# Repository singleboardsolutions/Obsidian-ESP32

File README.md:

# Obsidian-ESP32
Design Files for Obsidian ESP32

Copyright Single Board Solutions LLC 2019
Licensed under CERN OHL v.1.2

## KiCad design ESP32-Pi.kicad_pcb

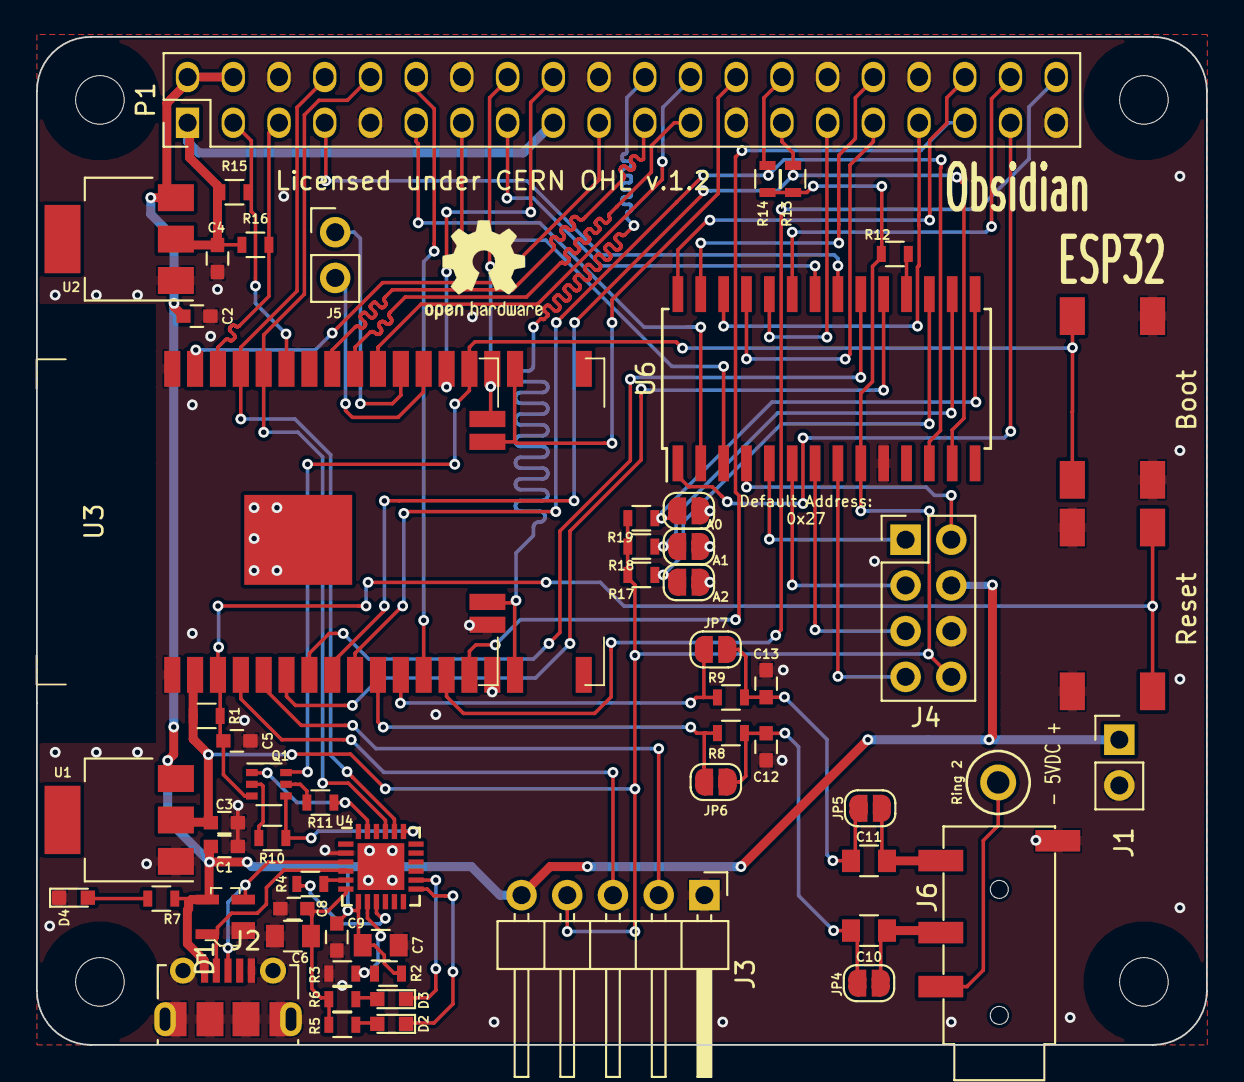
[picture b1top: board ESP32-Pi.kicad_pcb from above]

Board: 2 copper layers, 65.0 x 56.0 mm, 63 parts (0 on the bottom side), 71 nets.

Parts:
C1, C2: .22uF; C_0603
C3, C4, C5: .1uF; C_0603
C6, C7: 4.7uF; C_0805
C8, C9: 100nF; C_0603
C10, C11: 10 uF; C_0805
C12, C13: 10n; C_0603
D1: SP0503BAHTG; SOT-143-4
D2: LED_Green; LED_0603
D3: LED_Red; LED_0603
D4: LED_yellow; LED_0603
J1: PHX MPT 2.54mm 2pol; Pin_Header_Straight_1x02_Pitch2.54mm
J2: USB_B_Micro; USB_Micro-B_Molex-105017-0001
J3: 2.54mm 1x05 right angle; Pin_Header_Angled_1x05_Pitch2.54mm
J4: 2.54mm 2x04 straight; Pin_Header_Straight_2x04_Pitch2.54mm
J5: IO16/17; Pin_Header_Straight_1x02_Pitch2.54mm
J6: PJ320D; PJ320D_3.5mm_Jack
JP1: A2; SolderJumper-2_P1.3mm_Open_RoundedPad1.0x1.5mm
JP2: A1; SolderJumper-2_P1.3mm_Open_RoundedPad1.0x1.5mm
JP3: A0; SolderJumper-2_P1.3mm_Open_RoundedPad1.0x1.5mm
JP4, JP5, JP6, JP7: Bypass; SolderJumper-2_P1.3mm_Open_RoundedPad1.0x1.5mm
MK1, MK2, MK3, MK4: M2.5; MountingHole_2.7mm_M2.5
P1: 2.54mm 2x20 straight; PinHeader_2x20_P2.54mm_Vertical
Q1: MBT3904DW1; SOT-363_SC-70-6
R1, R4, R10, R11, R12, R17, R18, R19: 10k; R_0603
R2: 22.1k; R_0603
R3: 47.5k; R_0603
R5, R6, R7: 1k; R_0603
R8, R9: 220; R_0603
R13, R14, R15, R16: 1.8k; R_0603
Ring 2: Test_Point_Keystone_5010-5014_Multipurpose
SW1, SW2: 2-1437565-7; SW_FSM_JSM
U1, U2: AP2114H-3.3; SOT-223
U3: ESP32-WROOM-32; ESP32-WROOMVER-32D
U4: CP2102N-A01-GQFN24; QFN-24-1EP_4x4mm_Pitch0.5mm
U6: MCP23017_SO; SOIC-28W_7.5x17.9mm_Pitch1.27mm

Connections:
+3.3VP: C4.1, P1.1, P1.17, R15.1, R16.1, U2.2
+3V3: C3.1, J3.4, J4.8, R1.1, R12.1, R13.1, R14.1, R17.2, R18.2, R19.2, U1.2, U3.2, U6.9
+5V: C1.1, C2.1, C7.1, C9.1, D1.3, J1.1, J2.1, J3.5, J4.4, P1.2, P1.4, R2.1, R7.2, U1.3, U2.3, U4.7
/BCLK: P1.12, U3.12
/BOOT: Q1.6, SW1.1, U3.25
/DTR_PROG: Q1.1, R11.2, U4.23
/Exp_A0: JP3.1, R19.1, U6.15
/Exp_A1: JP2.1, R18.1, U6.16
/Exp_A2: JP1.1, R17.1, U6.17
/GPIO4(GCLK): P1.7, U6.21
/GPIO5: P1.29, U6.24
/GPIO6: P1.31, U6.25
/GPIO12(PWM0): P1.32, U6.27
/GPIO13(PWM1): P1.33, U6.26
/GPIO16: P1.36, U6.28
/GPIO17: P1.11, U6.2
/GPIO22(GEN3): P1.15, U6.22
/GPIO25(GEN6): P1.38, U6.23
/GPIO26: P1.37, U6.1
/GPIO27: P1.13, U6.3
/HSPI_MISO: P1.35, U3.14
/HSPI_MOSI: P1.22, U3.16
/HSPI_SCK: P1.40, U3.13
/HSPI_SS: P1.26, U3.23
/I34: U3.6, U6.19
/I35: U3.7, U6.20
/ID_SC: P1.28, R14.2, U3.9, U6.12
/ID_SD: P1.27, R13.2, U3.8, U6.13
/IO2: P1.16, U3.24
/IO4: P1.18, U3.26
/L_FILT: C11.1, C13.1, JP5.1, JP7.2, R9.1
/RESET: C5.1, Q1.3, R1.2, SW2.2, U3.3
/RTS_PROG: Q1.4, R10.2, U4.19
/RXD: P1.10, U3.34, U4.21
/R_FILT: C10.2, C12.1, JP4.1, JP6.2, R8.1
/SCL: P1.5, R16.2, U3.36
/SDA: P1.3, R15.2, U3.33
/S_VN: J3.2, U3.5
/S_VP: J3.3, U3.4
/TXD: P1.8, U3.35, U4.20
/USBD+: D1.2, J2.3, U4.3
/USBD-: D1.4, J2.2, U4.4
/VSPI_MISO: P1.21, U3.31
/VSPI_MOSI: P1.19, U3.37
/VSPI_SCK: P1.23, U3.30
/VSPI_SS: P1.24, U3.29
/left: JP7.1, R9.2, U3.11
/right: JP6.1, R8.2, U3.10
GND: C1.2, C2.2, C3.2, C4.2, C5.2, C6.2, C7.2, C8.2, C9.2, C12.2, C13.2, D1.1, D4.1, J1.2, J2.5, J2.6, J3.1, J4.6, J6.S, JP1.2, JP2.2, JP3.2, P1.6, P1.9, P1.14, P1.20, P1.25, P1.30, P1.34, P1.39, R3.2, SW1.2, SW2.1, U1.1, U2.1, U3.1, U3.15, U3.38, U4.2, U4.25, U6.10
unnamed: C10.1, J6.R1, JP4.2
unnamed: C11.2, J6.T, JP5.2
unnamed: D2.1, U4.13
unnamed: D2.2, R5.1
unnamed: D3.1, U4.14
unnamed: D3.2, R6.1
unnamed: D4.2, R7.1
unnamed: J4.1, U6.5
unnamed: J4.2, U6.4
unnamed: J4.3, U6.6
unnamed: J4.5, U6.7
unnamed: J4.7, U6.8
unnamed: J5.1, U3.28
unnamed: J5.2, U3.27
unnamed: J6.R2, Ring 2.1
unnamed: Q1.2, R10.1
unnamed: Q1.5, R11.1
unnamed: R2.2, R3.1, U4.8
unnamed: R4.1, U4.5
unnamed: R4.2, U4.9
unnamed: R12.2, U6.18
VDD: C6.1, C8.1, R5.2, R6.2, U4.6

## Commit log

2019-11-06 Add CERN OHL license
    Adding Licence and "howto"
2020-04-06 updates
    Documentation adjustments

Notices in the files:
ESP32-Pi.kicad_pcb:
This document describes Open Hardware and is licensed under the CERN OHL v. 1.2
Copyright Thomas McKahan 2019
You may redistribute and modify this documentation under the
terms of the CERN OHL v.1.2. This document is distributed
